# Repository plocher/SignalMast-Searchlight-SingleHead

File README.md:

# SignalMast-CL-SingleHead
## License: CERN Open Hardware Licence v1.2

Low cost Color Light (Single lens) single high head Signal Mast - N scale

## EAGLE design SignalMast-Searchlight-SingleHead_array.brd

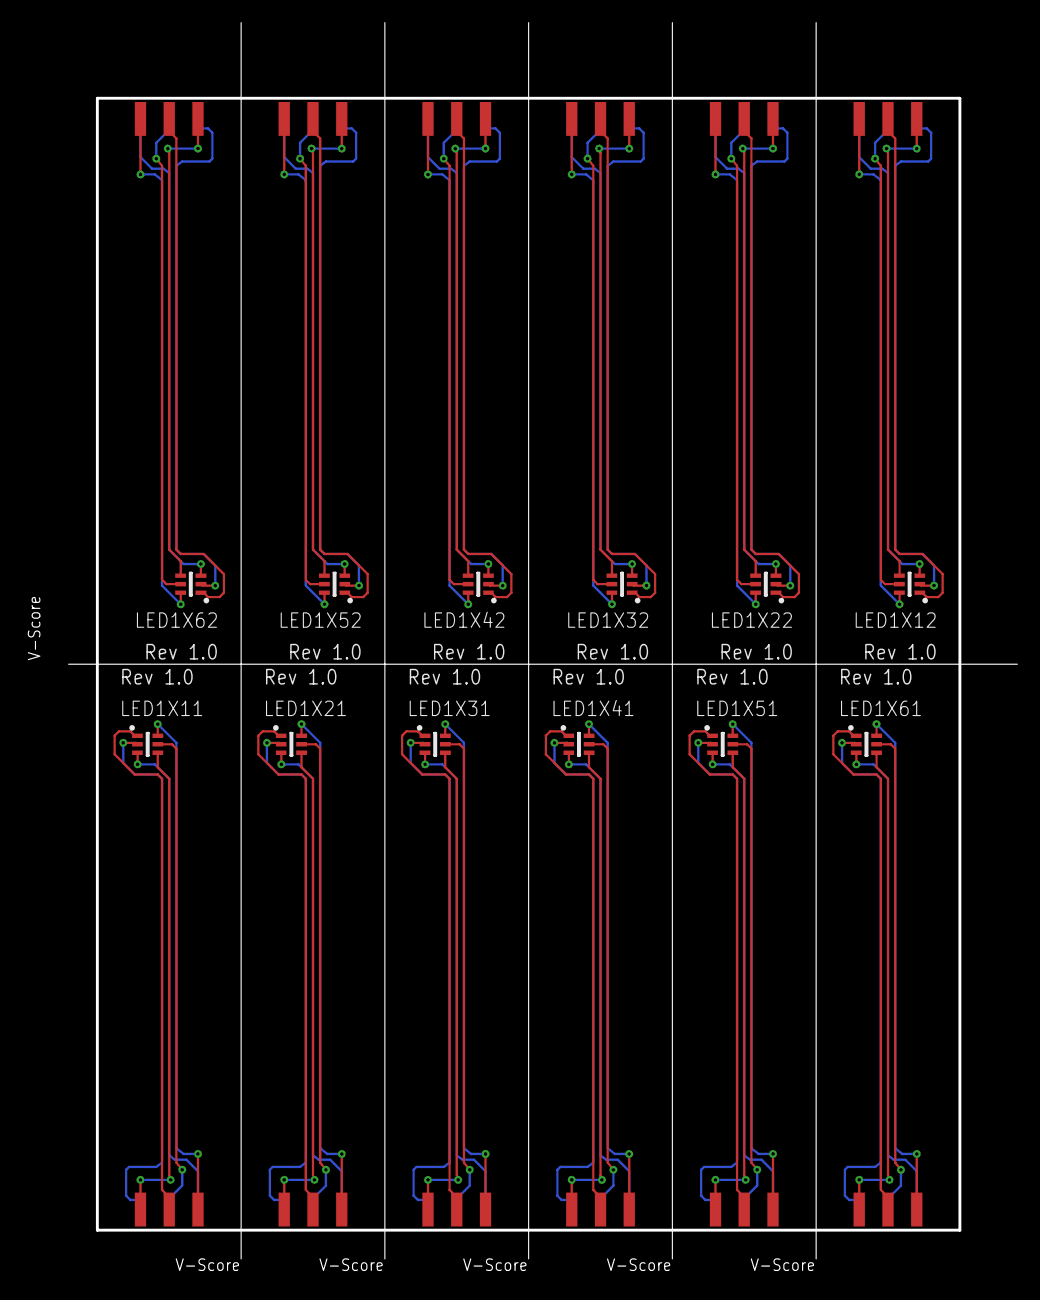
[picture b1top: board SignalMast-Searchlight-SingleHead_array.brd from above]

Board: 2 copper layers, 87.6 x 110.6 mm, 24 parts (0 on the bottom side), 72 nets.

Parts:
CON1X11, CON1X12, CON1X21, CON1X22, CON1X31, CON1X32, CON1X41, CON1X42, CON1X51, CON1X52, CON1X61, CON1X62: 2x3-0.100; 2X3-SMD_EDGE
LED1X11, LED1X12, LED1X21, LED1X22, LED1X31, LED1X32, LED1X41, LED1X42, LED1X51, LED1X52, LED1X61, LED1X62: RGB; APA102

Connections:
CINX11: CON1X11.2, LED1X11.2
CINX12: CON1X12.2, LED1X12.2
CINX21: CON1X21.2, LED1X21.2
CINX22: CON1X22.2, LED1X22.2
CINX31: CON1X31.2, LED1X31.2
CINX32: CON1X32.2, LED1X32.2
CINX41: CON1X41.2, LED1X41.2
CINX42: CON1X42.2, LED1X42.2
CINX51: CON1X51.2, LED1X51.2
CINX52: CON1X52.2, LED1X52.2
CINX61: CON1X61.2, LED1X61.2
CINX62: CON1X62.2, LED1X62.2
COUTX11: CON1X11.4, LED1X11.5
COUTX12: CON1X12.4, LED1X12.5
COUTX21: CON1X21.4, LED1X21.5
COUTX22: CON1X22.4, LED1X22.5
COUTX31: CON1X31.4, LED1X31.5
COUTX32: CON1X32.4, LED1X32.5
COUTX41: CON1X41.4, LED1X41.5
COUTX42: CON1X42.4, LED1X42.5
COUTX51: CON1X51.4, LED1X51.5
COUTX52: CON1X52.4, LED1X52.5
COUTX61: CON1X61.4, LED1X61.5
COUTX62: CON1X62.4, LED1X62.5
DINX11: CON1X11.3, LED1X11.1
DINX12: CON1X12.3, LED1X12.1
DINX21: CON1X21.3, LED1X21.1
DINX22: CON1X22.3, LED1X22.1
DINX31: CON1X31.3, LED1X31.1
DINX32: CON1X32.3, LED1X32.1
DINX41: CON1X41.3, LED1X41.1
DINX42: CON1X42.3, LED1X42.1
DINX51: CON1X51.3, LED1X51.1
DINX52: CON1X52.3, LED1X52.1
DINX61: CON1X61.3, LED1X61.1
DINX62: CON1X62.3, LED1X62.1
DOUTX11: CON1X11.5, LED1X11.6
DOUTX12: CON1X12.5, LED1X12.6
DOUTX21: CON1X21.5, LED1X21.6
DOUTX22: CON1X22.5, LED1X22.6
DOUTX31: CON1X31.5, LED1X31.6
DOUTX32: CON1X32.5, LED1X32.6
DOUTX41: CON1X41.5, LED1X41.6
DOUTX42: CON1X42.5, LED1X42.6
DOUTX51: CON1X51.5, LED1X51.6
DOUTX52: CON1X52.5, LED1X52.6
DOUTX61: CON1X61.5, LED1X61.6
DOUTX62: CON1X62.5, LED1X62.6
GNDX11: CON1X11.6, LED1X11.3
GNDX12: CON1X12.6, LED1X12.3
GNDX21: CON1X21.6, LED1X21.3
GNDX22: CON1X22.6, LED1X22.3
GNDX31: CON1X31.6, LED1X31.3
GNDX32: CON1X32.6, LED1X32.3
GNDX41: CON1X41.6, LED1X41.3
GNDX42: CON1X42.6, LED1X42.3
GNDX51: CON1X51.6, LED1X51.3
GNDX52: CON1X52.6, LED1X52.3
GNDX61: CON1X61.6, LED1X61.3
GNDX62: CON1X62.6, LED1X62.3
VCCX11: CON1X11.1, LED1X11.4
VCCX12: CON1X12.1, LED1X12.4
VCCX21: CON1X21.1, LED1X21.4
VCCX22: CON1X22.1, LED1X22.4
VCCX31: CON1X31.1, LED1X31.4
VCCX32: CON1X32.1, LED1X32.4
VCCX41: CON1X41.1, LED1X41.4
VCCX42: CON1X42.1, LED1X42.4
VCCX51: CON1X51.1, LED1X51.4
VCCX52: CON1X52.1, LED1X52.4
VCCX61: CON1X61.1, LED1X61.4
VCCX62: CON1X62.1, LED1X62.4

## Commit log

2020-05-04 updated tags
2020-10-06 normalized values
